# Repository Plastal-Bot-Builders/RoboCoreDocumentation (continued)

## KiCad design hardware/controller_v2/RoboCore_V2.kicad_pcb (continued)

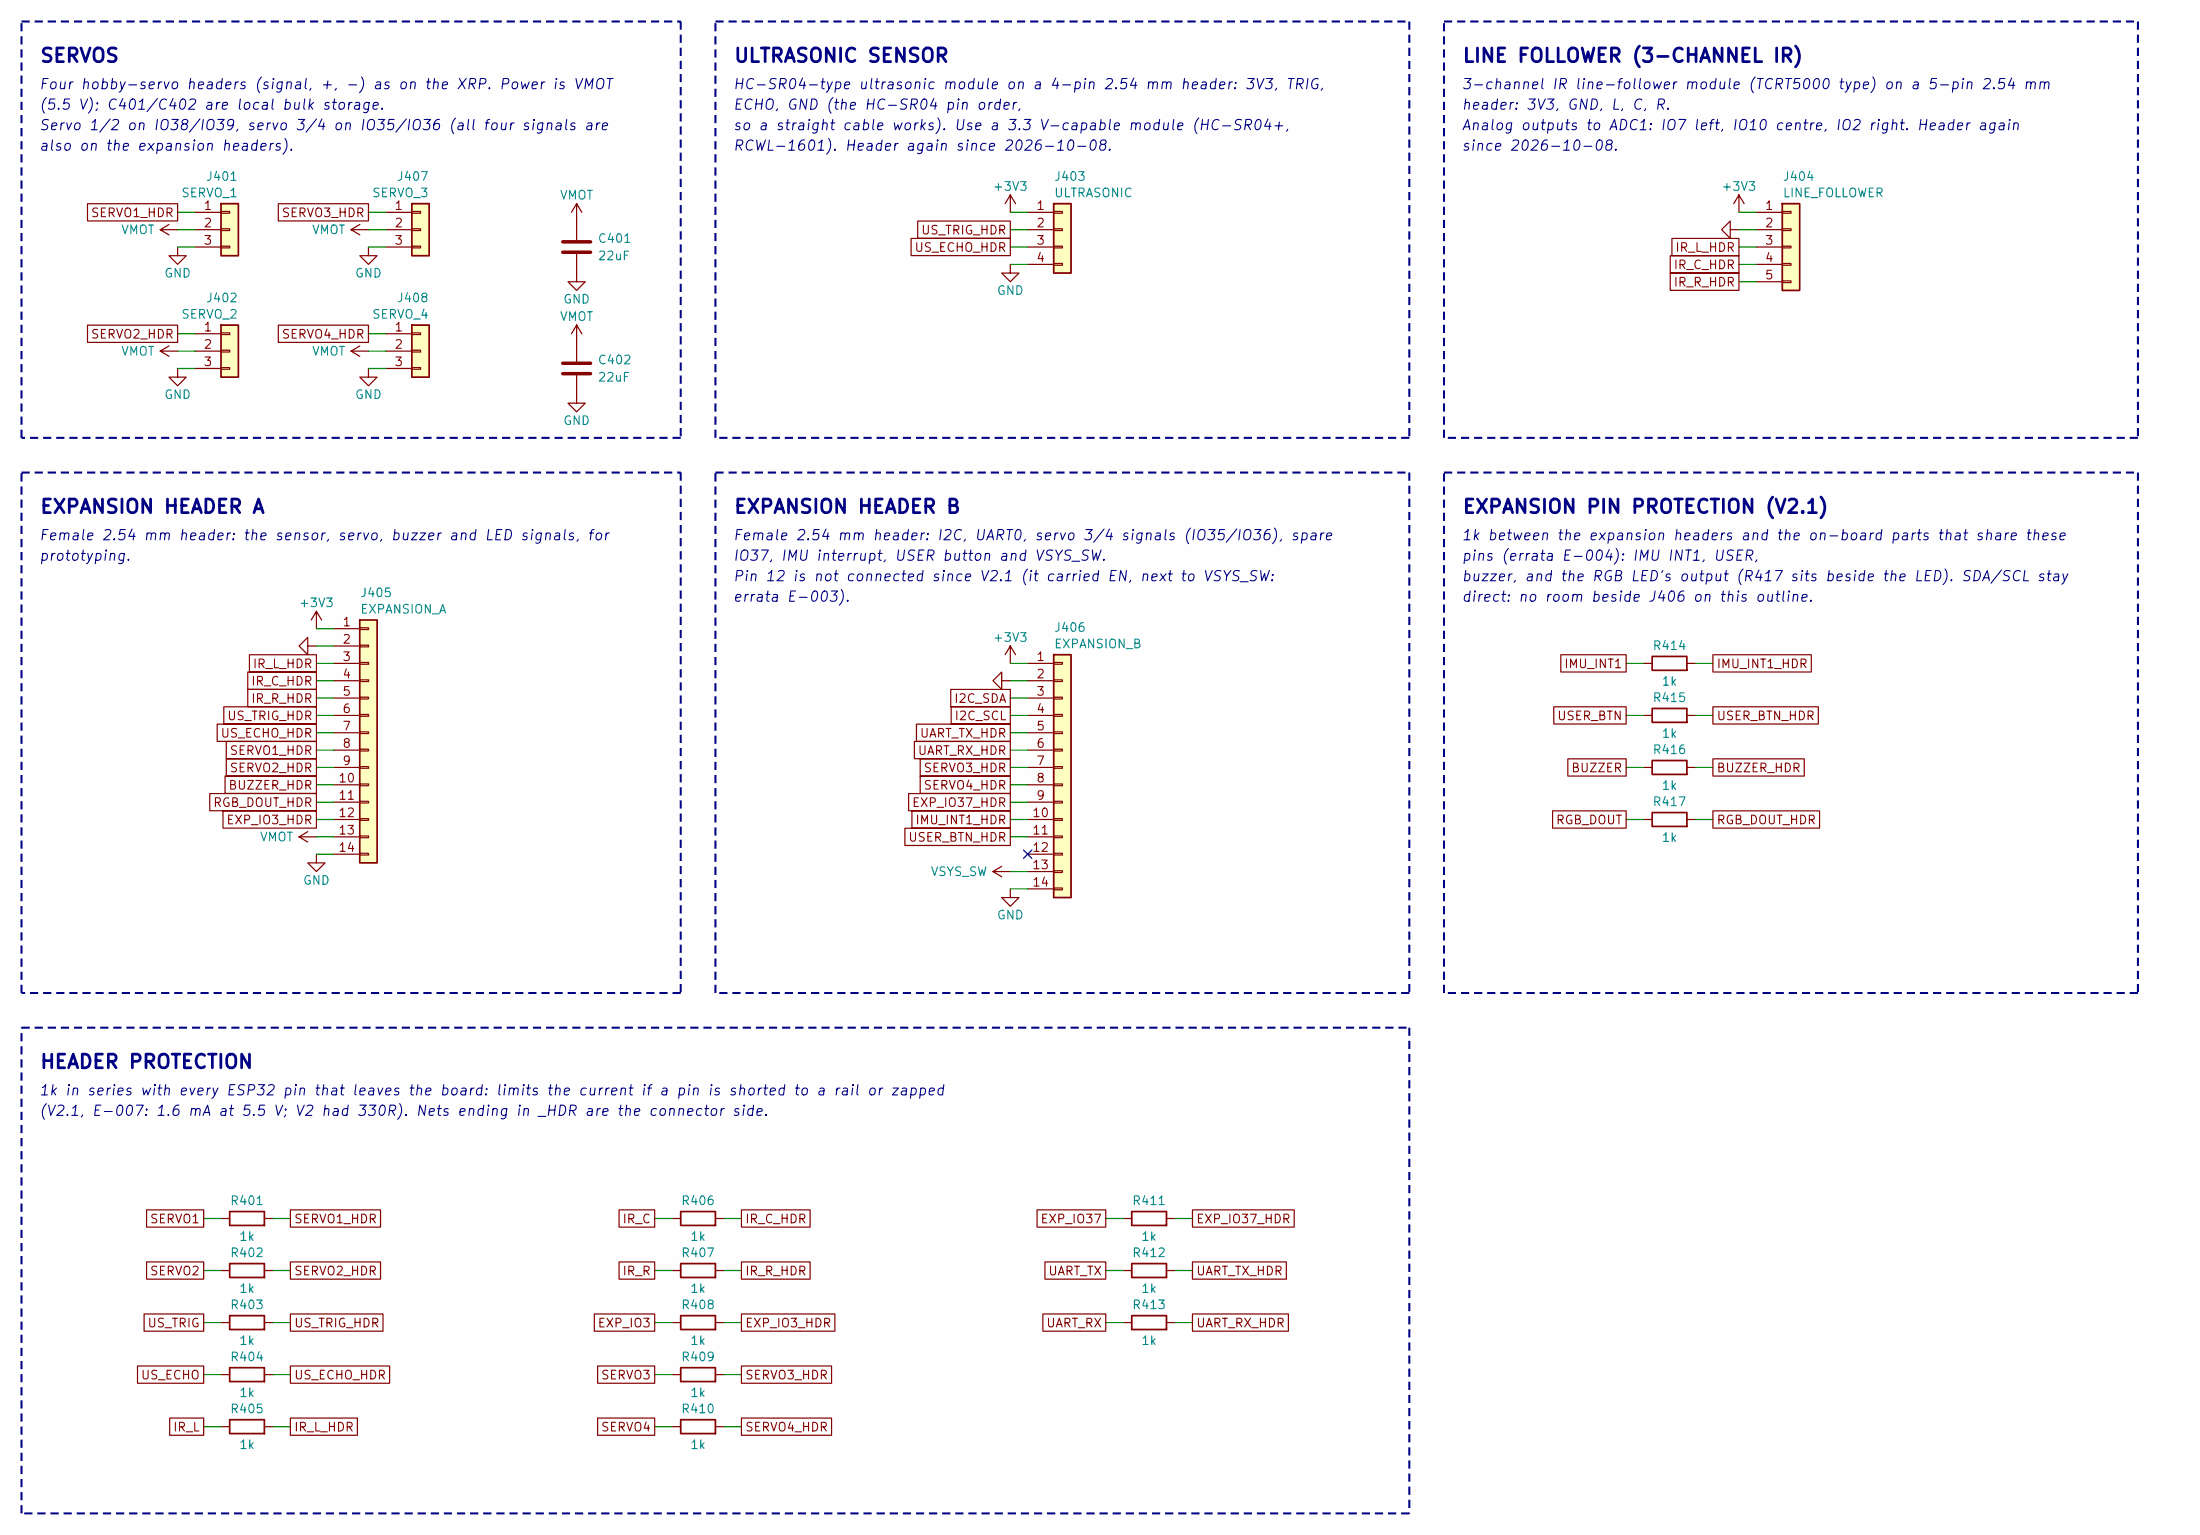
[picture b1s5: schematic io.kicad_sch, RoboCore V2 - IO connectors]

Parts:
C401, C402: 22uF; C_1206_3216Metric; LCSC C12891
J401: SERVO_1; PinHeader_1x03_P2.54mm_Vertical; LCSC C52016391
J402: SERVO_2; PinHeader_1x03_P2.54mm_Vertical; LCSC C52016391
J403: ULTRASONIC; PinHeader_1x04_P2.54mm_Vertical; LCSC C52016392
J404: LINE_FOLLOWER; PinHeader_1x05_P2.54mm_Vertical; LCSC C27985190
J405: EXPANSION_A; PinSocket_1x14_P2.54mm_Vertical; LCSC C22373900
J406: EXPANSION_B; PinSocket_1x14_P2.54mm_Vertical; LCSC C22373900
J407: SERVO_3; PinHeader_1x03_P2.54mm_Vertical; LCSC C52016391
J408: SERVO_4; PinHeader_1x03_P2.54mm_Vertical; LCSC C52016391
R401, R402, R403, R404, R405, R406, R407, R408, R409, R410, R411, R412, R413, R414, R415, R416, R417: 1k; R_0402_1005Metric; LCSC C106235

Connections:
+3V3: J403.1, J404.1, J405.1, J406.1; also elsewhere on the board
BUZZER: R416.1; also elsewhere on the board
BUZZER_HDR: J405.10, R416.2
EXP_IO3: R408.1; also elsewhere on the board
EXP_IO3_HDR: J405.12, R408.2
EXP_IO37: R411.1; also elsewhere on the board
EXP_IO37_HDR: J406.9, R411.2
GND: C401.2, C402.2, J401.3, J402.3, J403.4, J404.2, J405.2, J405.14, J406.2, J406.14, J407.3, J408.3; also elsewhere on the board
I2C_SCL: J406.4; also elsewhere on the board
I2C_SDA: J406.3; also elsewhere on the board
IMU_INT1: R414.1; also elsewhere on the board
IMU_INT1_HDR: J406.10, R414.2
IR_C: R406.1; also elsewhere on the board
IR_C_HDR: J404.4, J405.4, R406.2
IR_L: R405.1; also elsewhere on the board
IR_L_HDR: J404.3, J405.3, R405.2
IR_R: R407.1; also elsewhere on the board
IR_R_HDR: J404.5, J405.5, R407.2
RGB_DOUT: R417.1; also elsewhere on the board
RGB_DOUT_HDR: J405.11, R417.2
SERVO1: R401.1; also elsewhere on the board
SERVO1_HDR: J401.1, J405.8, R401.2
SERVO2: R402.1; also elsewhere on the board
SERVO2_HDR: J402.1, J405.9, R402.2
SERVO3: R409.1; also elsewhere on the board
SERVO3_HDR: J406.7, J407.1, R409.2
SERVO4: R410.1; also elsewhere on the board
SERVO4_HDR: J406.8, J408.1, R410.2
UART_RX: R413.1; also elsewhere on the board
UART_RX_HDR: J406.6, R413.2
UART_TX: R412.1; also elsewhere on the board
UART_TX_HDR: J406.5, R412.2
USER_BTN: R415.1; also elsewhere on the board
USER_BTN_HDR: J406.11, R415.2
US_ECHO: R404.1; also elsewhere on the board
US_ECHO_HDR: J403.3, J405.7, R404.2
US_TRIG: R403.1; also elsewhere on the board
US_TRIG_HDR: J403.2, J405.6, R403.2
VMOT: C401.1, C402.1, J401.2, J402.2, J405.13, J407.2, J408.2; also elsewhere on the board
VSYS_SW: J406.13; also elsewhere on the board

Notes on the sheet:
SERVOS
Four hobby-servo headers (signal, +, -) as on the XRP. Power is VMOT
(5.5 V); C401/C402 are local bulk storage.
Servo 1/2 on IO38/IO39, servo 3/4 on IO35/IO36 (all four signals are
also on the expansion headers).
ULTRASONIC SENSOR
HC-SR04-type ultrasonic module on a 4-pin 2.54 mm header: 3V3, TRIG,
ECHO, GND (the HC-SR04 pin order,
so a straight cable works). Use a 3.3 V-capable module (HC-SR04+,
RCWL-1601). Header again since 2026-10-08.
LINE FOLLOWER (3-CHANNEL IR)
3-channel IR line-follower module (TCRT5000 type) on a 5-pin 2.54 mm
header: 3V3, GND, L, C, R.
Analog outputs to ADC1: IO7 left, IO10 centre, IO2 right. Header again
since 2026-10-08.
EXPANSION HEADER A
Female 2.54 mm header: the sensor, servo, buzzer and LED signals, for
prototyping.
EXPANSION HEADER B
Female 2.54 mm header: I2C, UART0, servo 3/4 signals (IO35/IO36), spare
IO37, IMU interrupt, USER button and VSYS_SW.
Pin 12 is not connected since V2.1 (it carried EN, next to VSYS_SW:
errata E-003).
HEADER PROTECTION
1k in series with every ESP32 pin that leaves the board: limits the current if a pin is shorted to a rail or zapped
(V2.1, E-007: 1.6 mA at 5.5 V; V2 had 330R). Nets ending in _HDR are the connector side.
EXPANSION PIN PROTECTION (V2.1)
1k between the expansion headers and the on-board parts that share these
pins (errata E-004): IMU INT1, USER,
buzzer, and the RGB LED's output (R417 sits beside the LED). SDA/SCL stay
direct: no room beside J406 on this outline.

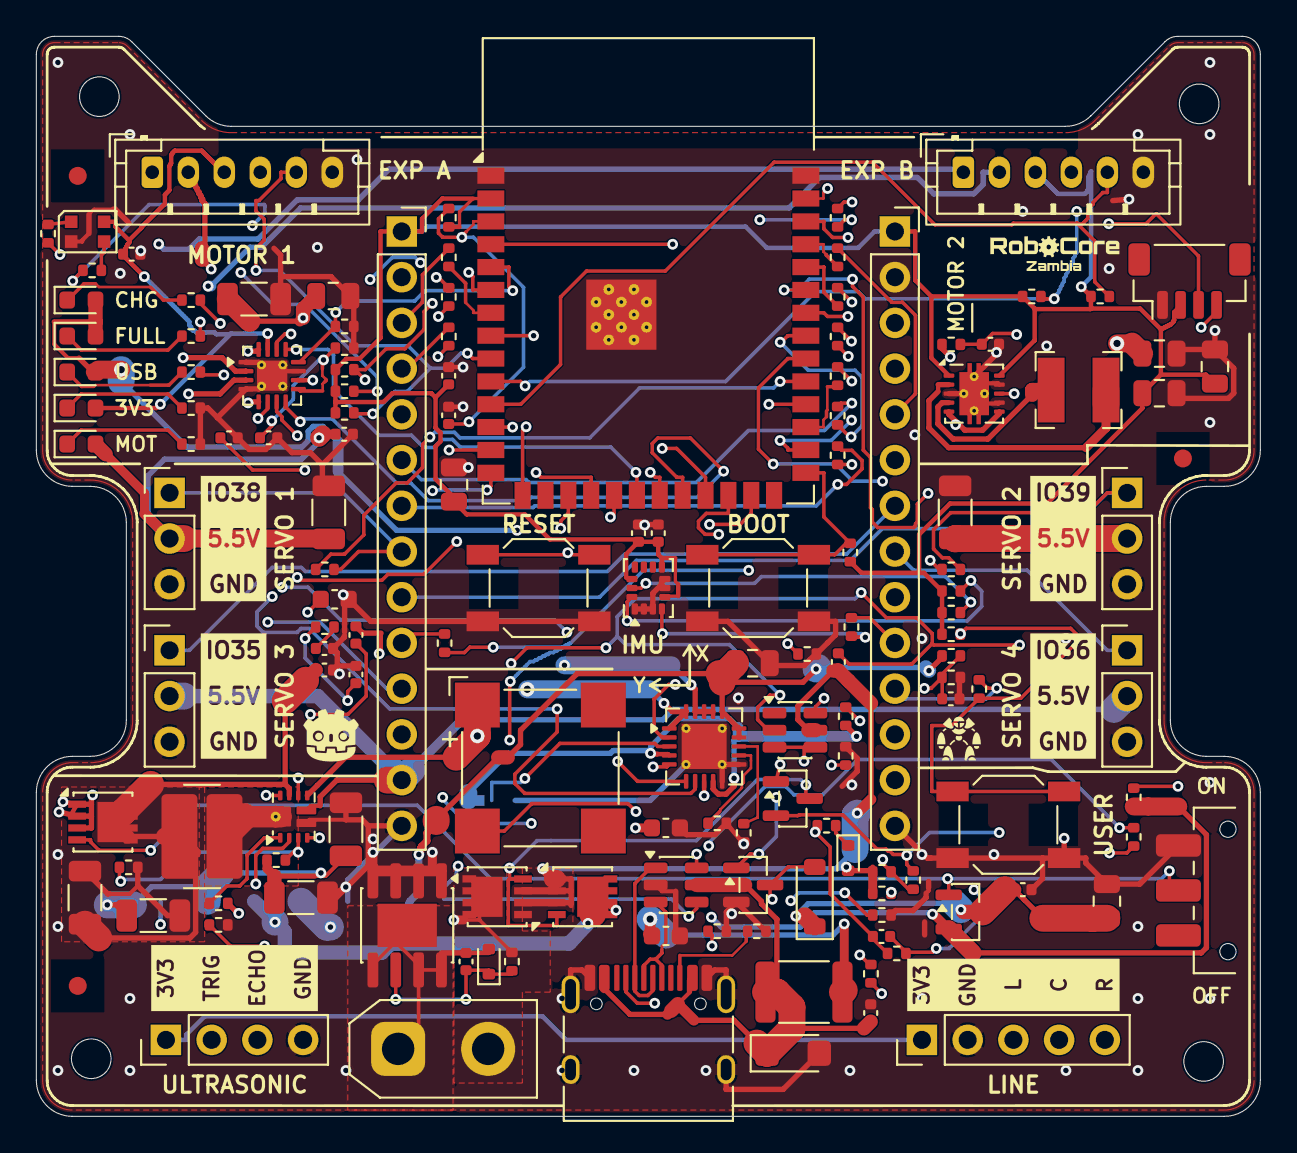
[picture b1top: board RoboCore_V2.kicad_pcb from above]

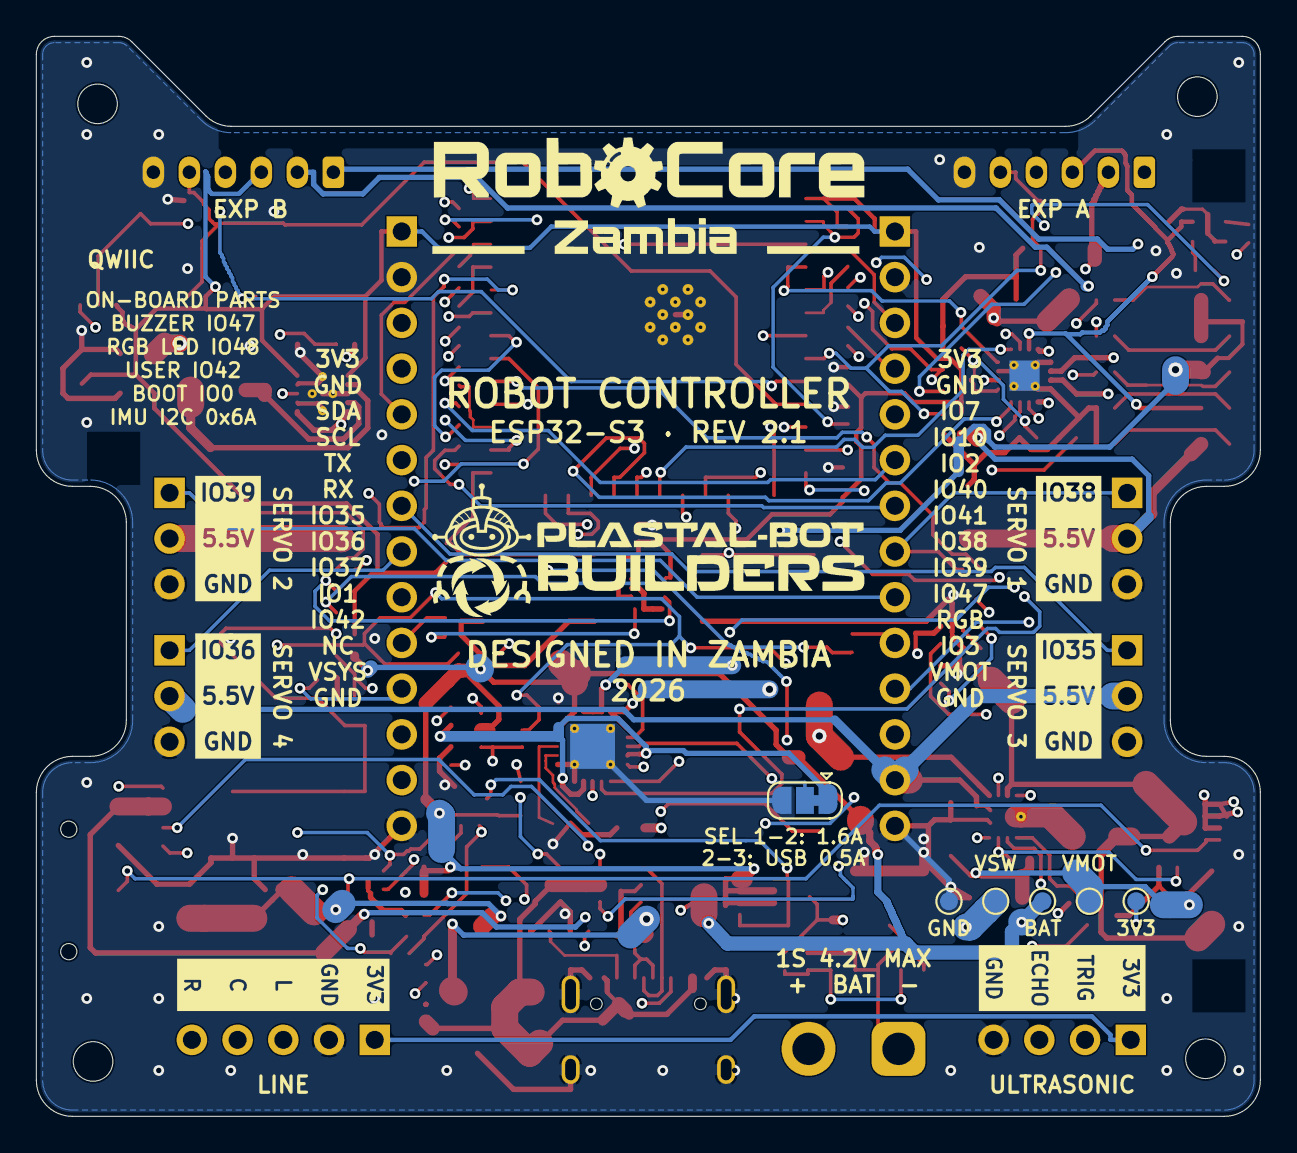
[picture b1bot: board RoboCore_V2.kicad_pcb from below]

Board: 4 copper layers, 68.0 x 60.0 mm, 154 parts (6 on the bottom side), 106 nets.

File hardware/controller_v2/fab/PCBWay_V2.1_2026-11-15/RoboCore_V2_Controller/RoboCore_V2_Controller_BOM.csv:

Item #,Designator,Qty,Manufacturer,Mfg Part #,Description / Value,Package/Footprint,Mounting Type,LCSC Part #,Notes
1,BZ201,1,Same Sky (CUI),CMT-8504-100-SMT-TR,Magnetic buzzer 8.5 mm (CMT-8504-100-SMT),MagneticBuzzer_CUI_CMT-8504-100-SMT,SMD,C22359707,"LCSC had only 12 (2026-10-07); Digi-Key has 30,000+."
2,"C101,C106,C107,C112,C114,C120,C122,C202,C204,C205,C206,C302",12,Samsung,CL05B104KB5NNNC,Ceramic capacitor 100nF 50V X7R ±10% 0402 (0.1uF),C_0402_1005Metric,SMD,C960916,
3,C102,1,Samsung,CL10A105KA8NNNC,Ceramic capacitor 1uF 25V X5R ±10% 0603 (1uF),C_0603_1608Metric,SMD,C5673,
4,C103,1,Samsung,CL10A106MO8NQNC,Ceramic capacitor 10uF 16V X5R ±20% 0603 (10uF),C_0603_1608Metric,SMD,C92487,
5,C104,1,Samsung,CL21A475KAQNNNE,Ceramic capacitor 4.7uF 25V X5R ±10% 0805 (4.7uF),C_0805_2012Metric,SMD,C1779,
6,"C105,C108,C301",3,Samsung,CL21A106KOQNNNE,Ceramic capacitor 10uF 16V X5R ±10% 0805 (10uF),C_0805_2012Metric,SMD,C1713,
7,"C109,C110,C201",3,Samsung,CL21A226MAQNNNE,Ceramic capacitor 22uF 25V X5R ±20% 0805 (22uF),C_0805_2012Metric,SMD,C45783,
8,"C111,C117,C118,C119,C303,C401,C402",7,Samsung,CL31A226KAHNNNE,Ceramic capacitor 22uF 25V X5R ±10% 1206 (22uF),C_1206_3216Metric,SMD,C12891,
9,C113,1,Samsung,CL10A225KO8NNNC,Ceramic capacitor 2.2uF 16V X5R ±10% 0603 (2.2uF),C_0603_1608Metric,SMD,C23630,
10,C115,1,Samsung,CL05B103KB5NNNC,Ceramic capacitor 10nF 50V X7R ±10% 0402 (10nF),C_0402_1005Metric,SMD,C15195,
11,C116,1,Samsung,CL05C220JB5NNNC,Ceramic capacitor 22pF 50V C0G ±5% 0402 (22pF),C_0402_1005Metric,SMD,C70464,
12,"C121,C203",2,Samsung,CL05A105KA5NNNC,Ceramic capacitor 1uF 25V X5R ±10% 0402 (1uF),C_0402_1005Metric,SMD,C16193167,
13,"C304,C305",2,Samsung,CL05B102KB5NNNC,Ceramic capacitor 1nF 50V X7R ±10% 0402 (1nF),C_0402_1005Metric,SMD,C14442,
14,"D101,D105",2,Lite-On,LTST-C191KRKT,LED red 0603 (RED),LED_0603_1608Metric,SMD,C125099,
15,"D102,D104",2,Lite-On,LTST-C191KGKT,LED green 0603 (GREEN),LED_0603_1608Metric,SMD,C125098,
16,D103,1,Lite-On,LTST-C191TBKT,LED blue 0603 (BLUE),LED_0603_1608Metric,SMD,C99290,
17,D106,1,Littelfuse,SMF5.0A,TVS diode 5 V (SMF5.0A),D_SMF,SMD,C151296,
18,D107,1,Vishay,1N4148WS-E3-08,Switching diode (1N4148WS),D_SOD-323,SMD,C129905,
19,D201,1,Worldsemi,WS2812B-2020-V6,Addressable RGB LED 2020 (WS2812B-2020),LED_WS2812B-2020_PLCC4_2.0x2.0mm,SMD,C52917434,
20,D202,1,Diodes Inc,1N4148W-7-F,Switching diode (1N4148W),D_SOD-123,SMD,C83528,
21,F101,1,Bourns,MF-MSMF150/24X-2,PTC resettable fuse 1.5 A (1.5A),Fuse_1812_4532Metric,SMD,C78695,
22,J101,1,HRO,TYPE-C-31-M-12,"USB-C receptacle, 16 pin (TYPE-C-31-M-12)",USB_C_Receptacle_HRO_TYPE-C-31-M-12,SMD,C165948,
23,J102,1,AMASS,XT30UPB-M,"Battery connector XT30, male, vertical (XT30UPB-M)",AMASS_XT30UPB-M_1x02_P5.0mm_Vertical,THT,C428721,"Through-hole, top side."
24,J201,1,JST,BM04B-SRSS-TB,JST SH 4-pin vertical header (Qwiic),JST_SH_BM04B-SRSS-TB_1x04-1MP_P1.00mm_Vertical,SMD,C160390,
25,"J301,J302",2,JST,BM06B-SRSS-TB,JST SH 6-pin vertical header (MOTOR_1 / MOTOR_2),JST_SH_BM06B-SRSS-TB_1x06-1MP_P1.00mm_Vertical_XRP,SMD,C160392,
26,"J401,J402,J407,J408",4,hanxia,HX PH254-01-03-Z-L11.5,"Pin header 1x3, 2.54 mm, straight (SERVO_1 / SERVO_2 / SERVO_3 / SERVO_4)",PinHeader_1x03_P2.54mm_Vertical,THT,C52016391,"Through-hole, top side, short end in the board (6 mm pin up)."
27,J403,1,hanxia,HX PH254-01-04-Z-L11.5,ULTRASONIC (ULTRASONIC),PinHeader_1x04_P2.54mm_Vertical,THT,C52016392,
28,J404,1,Hong Cheng,HC-PZ254-11.5L-1x5PZ,LINE_FOLLOWER (LINE_FOLLOWER),PinHeader_1x05_P2.54mm_Vertical,THT,C27985190,
29,"J405,J406",2,Hong Cheng,HC-PM254-8.5H-1x14PZ,"Female socket 1x14, 2.54 mm, 8.5 mm tall (EXPANSION_A / EXPANSION_B)",PinSocket_1x14_P2.54mm_Vertical,THT,C22373900,"Through-hole, top side."
30,L101,1,Bourns,SRN4018-2R2M,Power inductor 2.2 uH (2.2uH),L_Bourns-SRN4018,SMD,C913207,
31,L102,1,Bourns,SRP5030CA-2R2M,Power inductor 2.2 uH (2.2uH),L_Bourns_SRP5030CA,SMD,C2046809,
32,Q101,1,Alpha & Omega,AO3401A,P-channel MOSFET 30 V (AO3401A),SOT-23,SMD,C15127,
33,"Q102,Q103,Q104",3,Vishay,SI7655DN-T1-GE3,"P-channel MOSFET, PowerPAK 1212-8 (SI7655DN)",Vishay_PowerPAK_1212-8_Single,SMD,C727830,
34,"Q105,Q201",2,Alpha & Omega,AO3400A,N-channel MOSFET 30 V (AO3400A),SOT-23,SMD,C20917,
35,"R101,R102",2,UNI-ROYAL,0402WGF5101TCE,Chip resistor 5.1kΩ ±1% 0402 (5.1k),R_0402_1005Metric,SMD,C25905,
36,"R103,R106,R201,R202,R203,R303,R304,R305,R306,R307",10,UNI-ROYAL,0402WGF1002TCE,Chip resistor 10kΩ ±1% 0402 (10k),R_0402_1005Metric,SMD,C25744,
37,R104,1,UNI-ROYAL,0402WGF2673TCE,Chip resistor 267kΩ ±1% 0402 (267k),R_0402_1005Metric,SMD,C270622,
38,"R105,R107,R108,R109,R119,R401,R402,R403,R404,R405,R406,R407,R408,R409,R410,R411,R412,R413,R414,R415,R416,R417",22,YAGEO,RC0402FR-071KL,Chip resistor 1kΩ ±1% 0402 (1k),R_0402_1005Metric,SMD,C106235,
39,"R110,R117,R118,R121,R122,R123,R206",7,UNI-ROYAL,0402WGF1003TCE,Chip resistor 100kΩ ±1% 0402 (100k),R_0402_1005Metric,SMD,C25741,
40,"R111,R205",2,YAGEO,RC0402FR-07100RL,Chip resistor 100Ω ±1% 0402 (100),R_0402_1005Metric,SMD,C106232,
41,R112,1,UNI-ROYAL,0402WGF9101TCE,Chip resistor 9.1kΩ ±1% 0402 (9.1k),R_0402_1005Metric,SMD,C25926,
42,"R113,R115",2,UNI-ROYAL,0402WGF3003TCE,Chip resistor 300kΩ ±1% 0402 (300k),R_0402_1005Metric,SMD,C25774,
43,R114,1,UNI-ROYAL,0402WGF8452TCE,Chip resistor 84.5kΩ ±1% 0402 (84.5k),R_0402_1005Metric,SMD,C26988,
44,R116,1,UNI-ROYAL,0402WGF2003TCE,Chip resistor 200kΩ ±1% 0402 (200k),R_0402_1005Metric,SMD,C25764,
45,R120,1,UNI-ROYAL,0402WGF2201TCE,Chip resistor 2.2kΩ ±1% 0402 (2.2k),R_0402_1005Metric,SMD,C25879,
46,R124,1,UNI-ROYAL,0402WGF3303TCE,Chip resistor 330kΩ ±1% 0402 (330k),R_0402_1005Metric,SMD,C25778,
47,R125,1,UNI-ROYAL,0402WGF1004TCE,Chip resistor 1MΩ ±1% 0402 (1M),R_0402_1005Metric,SMD,C26083,
48,R126,1,UNI-ROYAL,0402WGF9532TCE,Chip resistor 95.3kΩ ±1% 0402 (95.3k),R_0402_1005Metric,SMD,C26990,
49,R204,1,YAGEO,RC0402FR-0733RL,Chip resistor 33Ω ±1% 0402 (33),R_0402_1005Metric,SMD,C138002,
50,"R207,R208",2,UNI-ROYAL,0402WGF4701TCE,Chip resistor 4.7kΩ ±1% 0402 (4.7k),R_0402_1005Metric,SMD,C25900,
51,"R301,R302",2,UNI-ROYAL,0402WGF1652TCE,Chip resistor 16.5kΩ ±1% 0402 (16.5k),R_0402_1005Metric,SMD,C25857,
52,SW101,1,C&K,JS102011SAQN,"Slide switch SPDT, side-actuated (ON/OFF)",SW_SPDT_CK_JS102011SAQN,SMD,C221660,"LCSC shows 0 stock (2026-10-07); Digi-Key has 54,000+. Lever must overhang the board edge as drawn."
53,"SW201,SW202,SW203",3,Alps Alpine,SKQGADE010,Tactile switch 5.2 x 5.2 mm (RESET / BOOT / USER),SW_SPST_SKQG_WithoutStem,SMD,C116647,
54,U101,1,STMicroelectronics,USBLC6-2SC6,"USB ESD protection, 2 lines (USBLC6-2SC6)",SOT-23-6,SMD,C7519,
55,U102,1,Microchip,MCP73871-2CCI/ML,"Li-ion charger with power path, 4.20 V charge voltage (MCP73871-2CCI/ML)",QFN-20-1EP_4x4mm_P0.5mm_EP2.5x2.5mm_ThermalVias,SMD,C5121473,Must be the -2 version (4.20 V). Other suffixes charge to the wrong voltage.
56,U103,1,Texas Instruments,TPS63001DRCR,"Buck-boost converter, 3.3 V fixed (TPS63001DRCR)",Texas_DRC0010J_ThermalVias,SMD,C28060,
57,U104,1,Texas Instruments,TPS61089RNRR,"Boost converter, 7 A switch (TPS61089RNRR)",Texas_VQFN-RNR0011A-11,SMD,C165129,
58,U105,1,Texas Instruments,TPS3700DDCR,Window voltage supervisor (TPS3700),TSOT-23-6,SMD,C33002,
59,U201,1,Espressif,ESP32-S3-WROOM-1-N8R2,"Wi-Fi/BLE module, 8 MB flash, 2 MB quad PSRAM (ESP32-S3-WROOM-1-N8R2)",ESP32-S3-WROOM-1,SMD,C2913204,Alternative: -N16R2. Do NOT use R8 / R16V (octal PSRAM) versions.
60,U202,1,STMicroelectronics,LSM6DSOXTR,"6-axis IMU (accelerometer + gyroscope), I2C (LSM6DSOX)",LGA-14_3x2.5mm_P0.5mm_LayoutBorder3x4y,SMD,C481766,
61,U301,1,Texas Instruments,DRV8411ARTER,"Dual H-bridge motor driver, 4 A (DRV8411ARTER)",WQFN-16-1EP_3x3mm_P0.5mm_EP1.68x1.68mm_ThermalVias,SMD,C18816315,

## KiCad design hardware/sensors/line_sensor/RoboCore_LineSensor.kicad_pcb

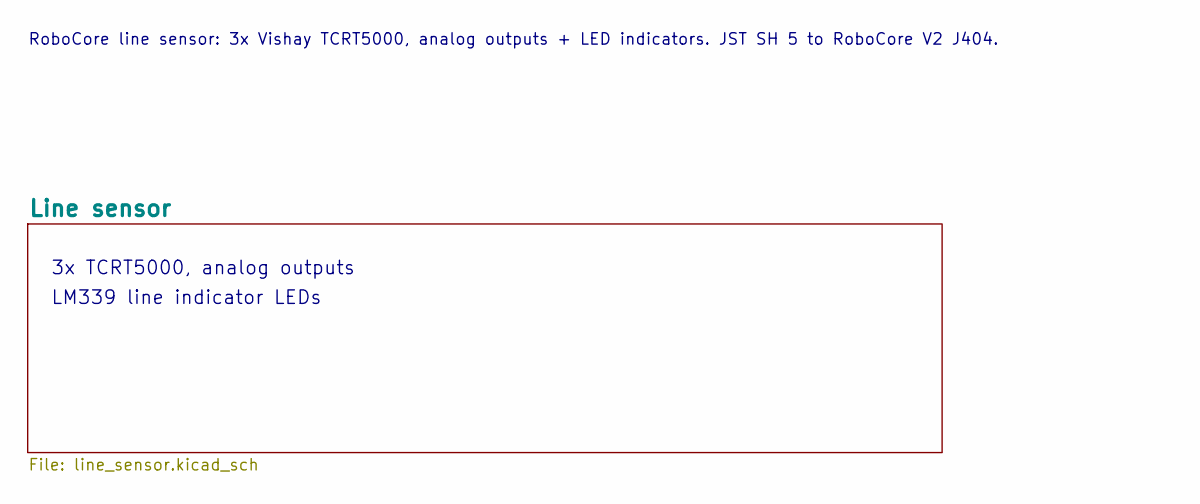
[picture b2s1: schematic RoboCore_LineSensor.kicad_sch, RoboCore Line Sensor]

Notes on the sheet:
3x TCRT5000, analog outputs
LM339 line indicator LEDs
RoboCore line sensor: 3x Vishay TCRT5000, analog outputs + LED indicators. JST SH 5 to RoboCore V2 J404.

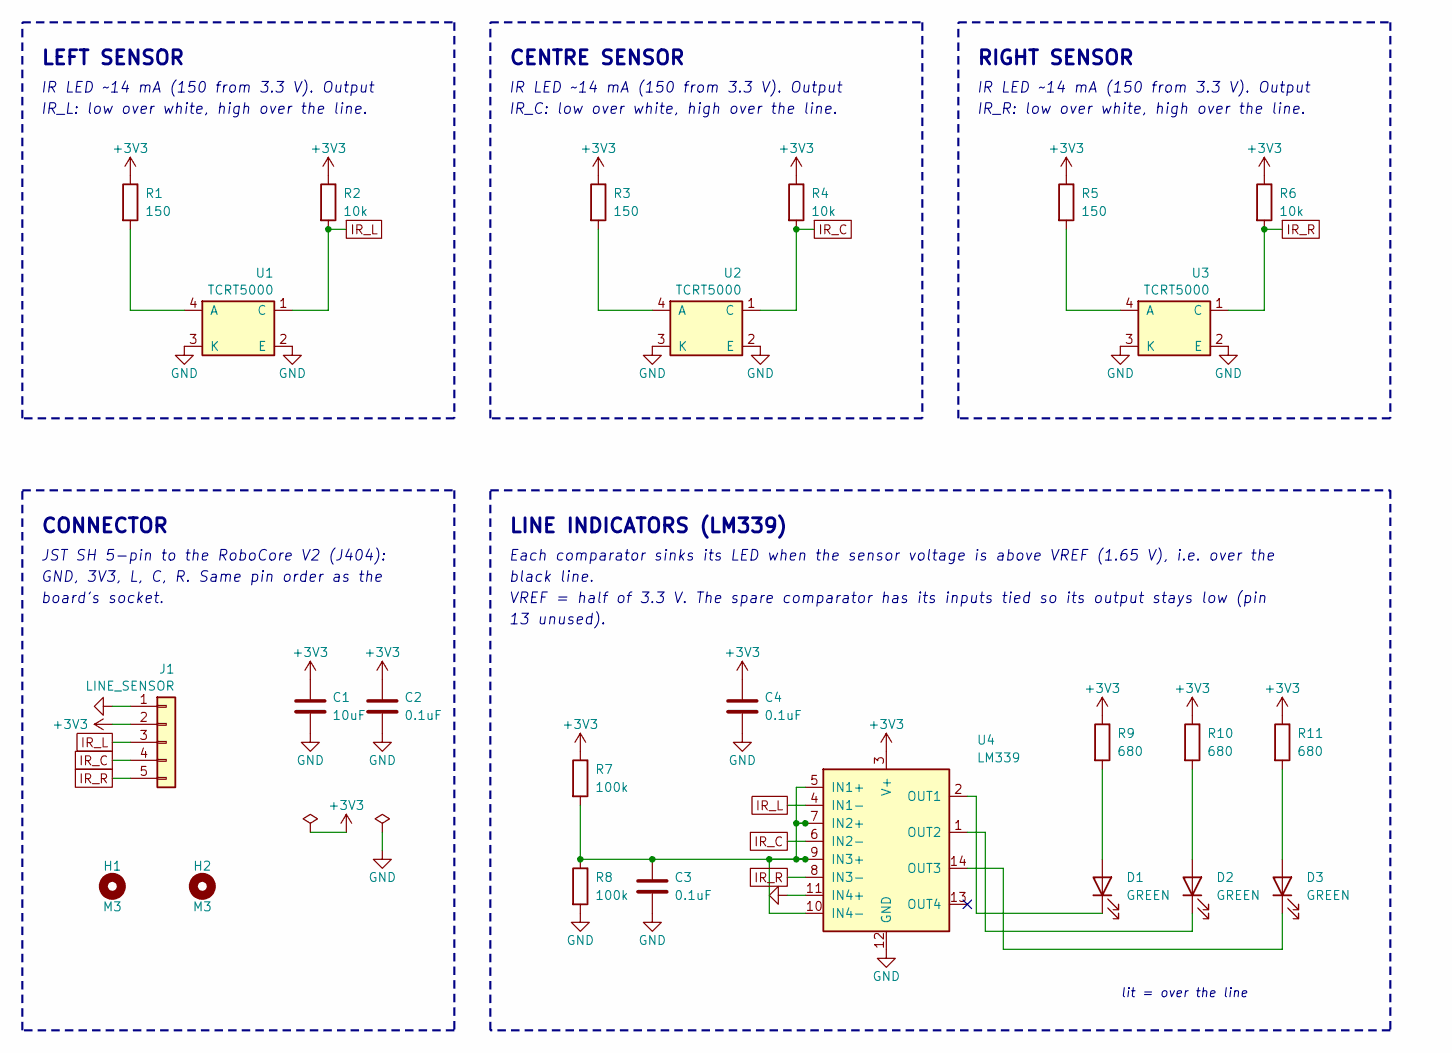
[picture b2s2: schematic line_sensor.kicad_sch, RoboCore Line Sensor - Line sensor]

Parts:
C1: 10uF; C_0805_2012Metric; LCSC C1713
C2, C3, C4: 0.1uF; C_0603_1608Metric; LCSC C1591
D1, D2, D3: GREEN; LED_0603_1608Metric; LCSC C125098
H1, H2: M3; MountingHole_3.2mm_M3
J1: LINE_SENSOR; JST_SH_BM05B-SRSS-TB_1x05-1MP_P1.00mm_Vertical; LCSC C160391
R1, R3, R5: 150; R_0603_1608Metric; LCSC C22808
R2, R4, R6: 10k; R_0603_1608Metric; LCSC C98220
R7, R8: 100k; R_0603_1608Metric; LCSC C25803
R9, R10, R11: 680; R_0603_1608Metric; LCSC C23228
U1, U2, U3: TCRT5000; Vishay_TCRT5000; LCSC C2984661
U4: LM339; SOIC-14_3.9x8.7mm_P1.27mm; LCSC C2829428

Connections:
+3V3: C1.1, C2.1, C4.1, J1.2, R1.1, R2.1, R3.1, R4.1, R5.1, R6.1, R7.1, R9.1, R10.1, R11.1, U4.3 (V+)
GND: C1.2, C2.2, C3.2, C4.2, J1.1, R8.2, U1.2 (E), U1.3 (K), U2.2 (E), U2.3 (K), U3.2 (E), U3.3 (K), U4.11 (IN4+), U4.12 (GND)
IR_C: J1.4, R4.2, U2.1 (C), U4.6 (IN2-)
IR_L: J1.3, R2.2, U1.1 (C), U4.4 (IN1-)
IR_R: J1.5, R6.2, U3.1 (C), U4.8 (IN3-)
unnamed: D1.2 (A), R9.2
unnamed: D1.1 (K), U4.2 (OUT1)
unnamed: D2.2 (A), R10.2
unnamed: D2.1 (K), U4.1 (OUT2)
unnamed: D3.2 (A), R11.2
unnamed: D3.1 (K), U4.14 (OUT3)
unnamed: R1.2, U1.4 (A)
unnamed: R3.2, U2.4 (A)
unnamed: R5.2, U3.4 (A)
unnamed: C3.1, R7.2, R8.1, U4.5 (IN1+), U4.7 (IN2+), U4.9 (IN3+), U4.10 (IN4-)

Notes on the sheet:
LEFT SENSOR
IR LED ~14 mA (150 from 3.3 V). Output
IR_L: low over white, high over the line.
CENTRE SENSOR
IR_C: low over white, high over the line.
RIGHT SENSOR
IR_R: low over white, high over the line.
CONNECTOR
JST SH 5-pin to the RoboCore V2 (J404):
GND, 3V3, L, C, R. Same pin order as the
board's socket.
LINE INDICATORS (LM339)
Each comparator sinks its LED when the sensor voltage is above VREF (1.65 V), i.e. over the
black line.
VREF = half of 3.3 V. The spare comparator has its inputs tied so its output stays low (pin
13 unused).
lit = over the line

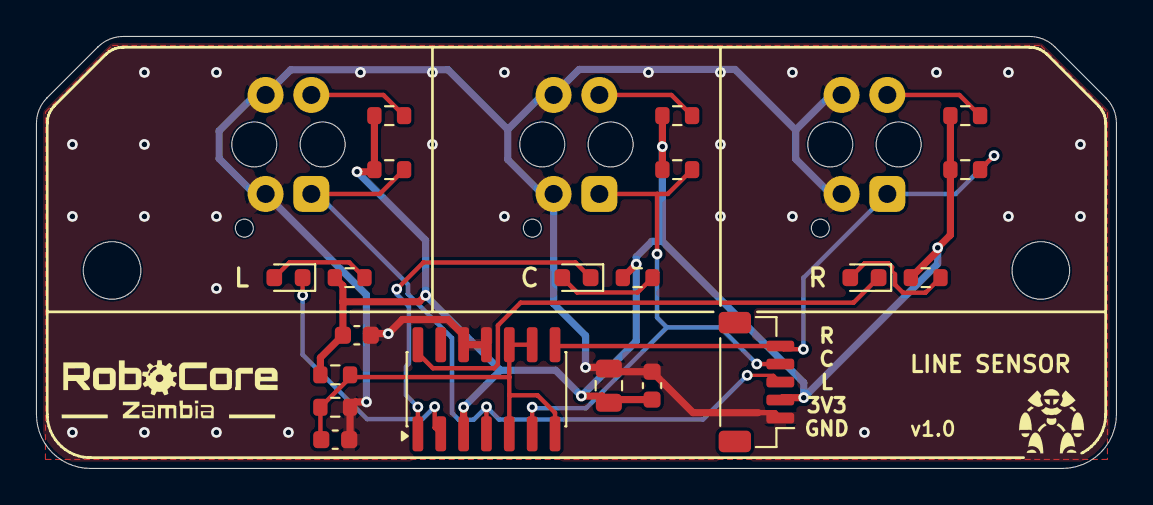
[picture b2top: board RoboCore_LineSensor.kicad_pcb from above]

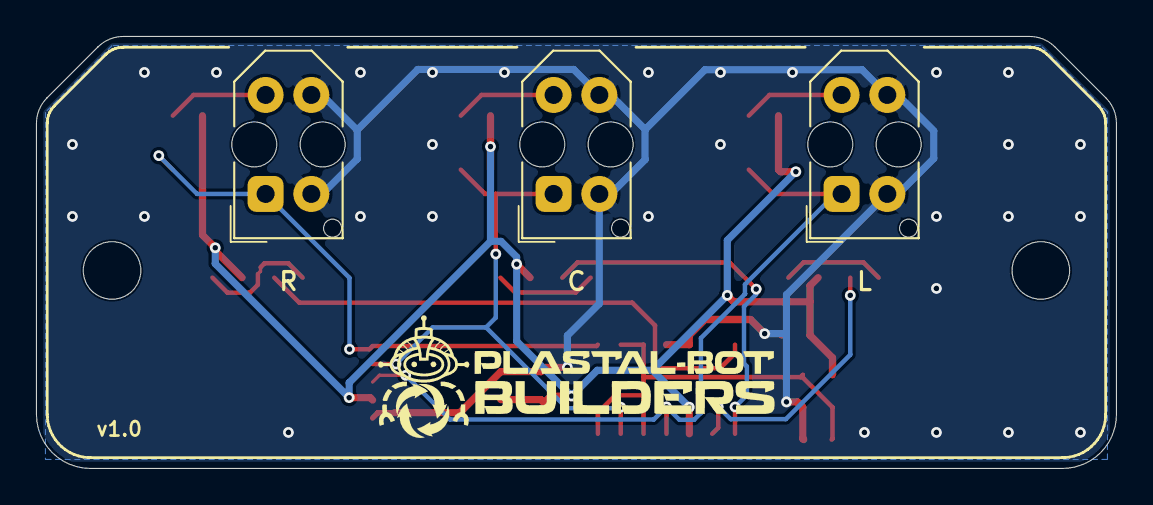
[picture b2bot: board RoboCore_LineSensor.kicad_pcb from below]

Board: 2 copper layers, 60.0 x 24.0 mm, 25 parts (3 on the bottom side), 15 nets.

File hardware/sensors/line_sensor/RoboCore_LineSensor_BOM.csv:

"Refs","Value","Footprint","Manufacturer","MPN","LCSC","Alternative","Qty"
"C1","10uF","Capacitor_SMD:C_0805_2012Metric","","","","","1"
"C2-C4","0.1uF","Capacitor_SMD:C_0603_1608Metric","","","","","3"
"D1-D3","GREEN","LED_SMD:LED_0603_1608Metric","Lite-On","LTST-C191KGKT","C125098","","3"
"J1","LINE_SENSOR","Connector_JST:JST_SH_BM05B-SRSS-TB_1x05-1MP_P1.00mm_Vertical","JST","BM05B-SRSS-TB","C160391","","1"
"R1,R3,R5","150","Resistor_SMD:R_0603_1608Metric","","","","","3"
"R2,R4,R6","10k","Resistor_SMD:R_0603_1608Metric","","","","","3"
"R7,R8","100k","Resistor_SMD:R_0603_1608Metric","","","","","2"
"R9-R11","680","Resistor_SMD:R_0603_1608Metric","","","","","3"
"U1-U3","TCRT5000","OptoDevice:Vishay_TCRT5000","Vishay","TCRT5000","C2984661","TCRT5000L (long leads)","3"
"U4","LM339","Package_SO:SOIC-14_3.9x8.7mm_P1.27mm","JSCJ","LM339","C2829428","TI LM339DR","1"

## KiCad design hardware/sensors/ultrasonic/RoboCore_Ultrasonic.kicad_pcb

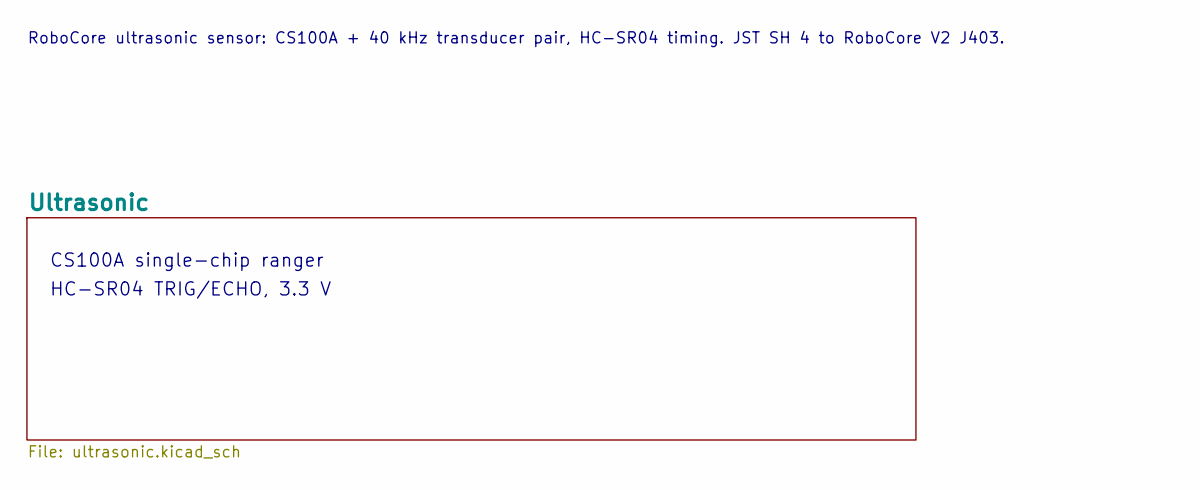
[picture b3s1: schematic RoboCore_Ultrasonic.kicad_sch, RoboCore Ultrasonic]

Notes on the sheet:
CS100A single-chip ranger
HC-SR04 TRIG/ECHO, 3.3 V
RoboCore ultrasonic sensor: CS100A + 40 kHz transducer pair, HC-SR04 timing. JST SH 4 to RoboCore V2 J403.

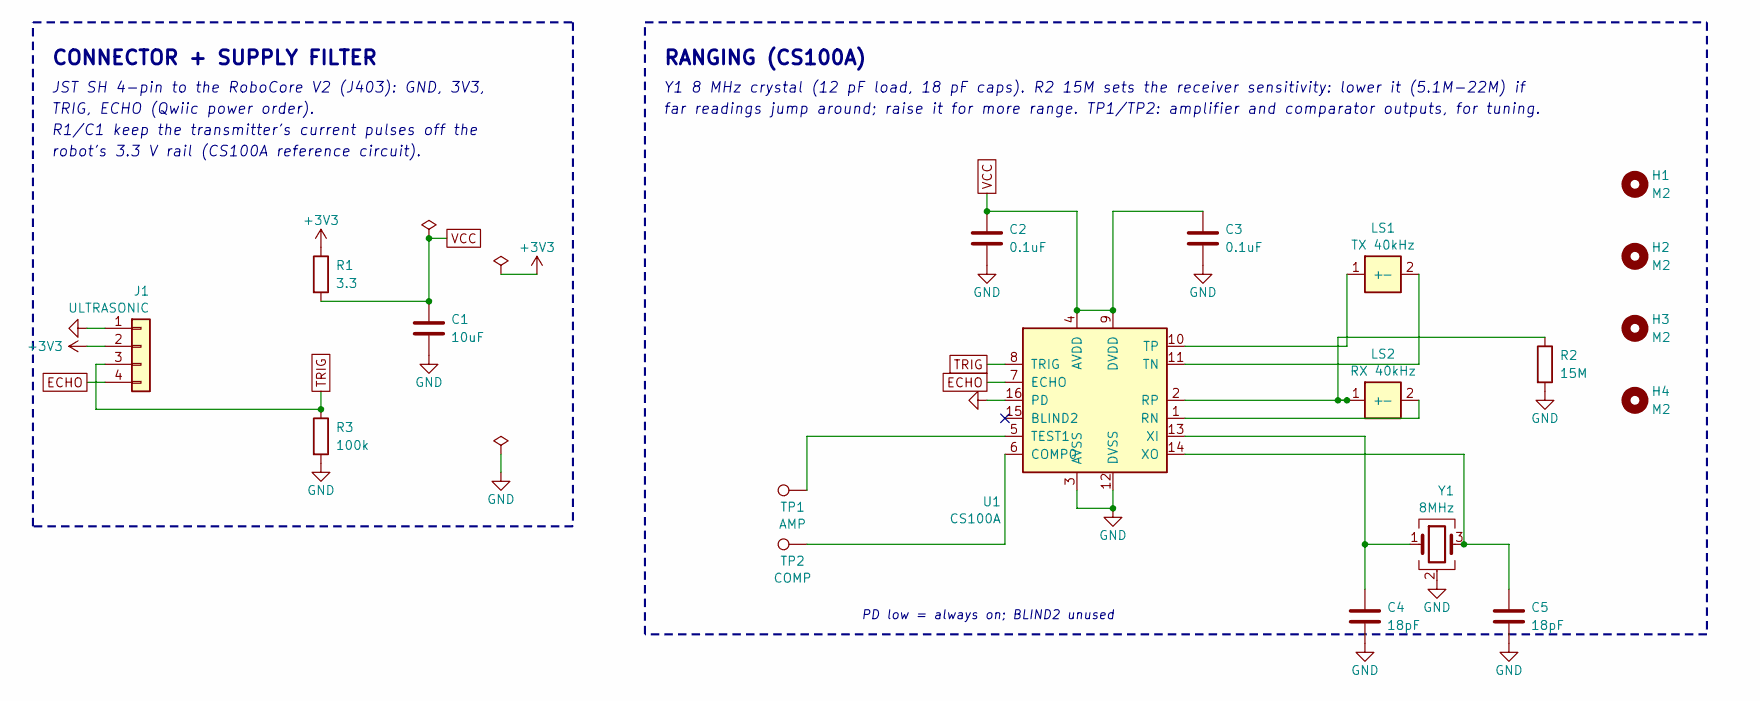
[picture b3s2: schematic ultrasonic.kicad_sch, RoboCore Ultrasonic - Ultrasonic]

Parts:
C1: 10uF; C_0805_2012Metric; LCSC C1713
C2, C3: 0.1uF; C_0603_1608Metric; LCSC C1591
C4, C5: 18pF; C_0603_1608Metric; LCSC C1647
H1, H2, H3, H4: M2; MountingHole_2.2mm_M2
J1: ULTRASONIC; JST_SH_BM04B-SRSS-TB_1x04-1MP_P1.00mm_Vertical; LCSC C160390
LS1: TX 40kHz; Ultrasonic_Transducer_D16.0mm_P10.00mm; LCSC C17701106
LS2: RX 40kHz; Ultrasonic_Transducer_D16.0mm_P10.00mm; LCSC C17701107
R1: 3.3; R_0603_1608Metric; LCSC C137725
R2: 15M; R_0603_1608Metric; LCSC C80615
R3: 100k; R_0603_1608Metric; LCSC C25803
TP1: AMP; TestPoint_Pad_D1.0mm
TP2: COMP; TestPoint_Pad_D1.0mm
U1: CS100A; SOIC-16_3.9x9.9mm_P1.27mm
Y1: 8MHz; Crystal_SMD_3225-4Pin_3.2x2.5mm; LCSC C2842191

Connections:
+3V3: J1.2, R1.1
ECHO: J1.4, U1.7 (ECHO)
GND: C1.2, C2.2, C3.2, C4.2, C5.2, J1.1, R2.2, R3.2, U1.3 (AVSS), U1.12 (DVSS), U1.16 (PD), Y1.2 (G), Y1.4 (G)
unnamed: LS1.1 (+), U1.10 (TP)
unnamed: LS1.2 (-), U1.11 (TN)
unnamed: LS2.1 (+), R2.1, U1.2 (RP)
unnamed: LS2.2 (-), U1.1 (RN)
unnamed: TP2.1, U1.6 (COMP0)
unnamed: TP1.1, U1.5 (TEST1)
unnamed: C4.1, U1.13 (XI), Y1.1
unnamed: C5.1, U1.14 (XO), Y1.3
TRIG: J1.3, R3.1, U1.8 (TRIG)
VCC: C1.1, C2.1, C3.1, R1.2, U1.4 (AVDD), U1.9 (DVDD)

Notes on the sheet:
CONNECTOR + SUPPLY FILTER
JST SH 4-pin to the RoboCore V2 (J403): GND, 3V3,
TRIG, ECHO (Qwiic power order).
R1/C1 keep the transmitter's current pulses off the
robot's 3.3 V rail (CS100A reference circuit).
RANGING (CS100A)
Y1 8 MHz crystal (12 pF load, 18 pF caps). R2 15M sets the receiver sensitivity: lower it (5.1M-22M) if
far readings jump around; raise it for more range. TP1/TP2: amplifier and comparator outputs, for tuning.
PD low = always on; BLIND2 unused

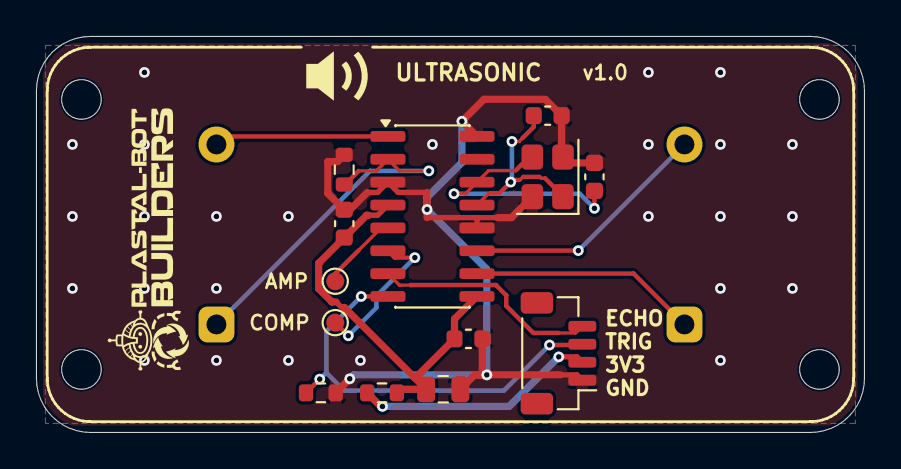
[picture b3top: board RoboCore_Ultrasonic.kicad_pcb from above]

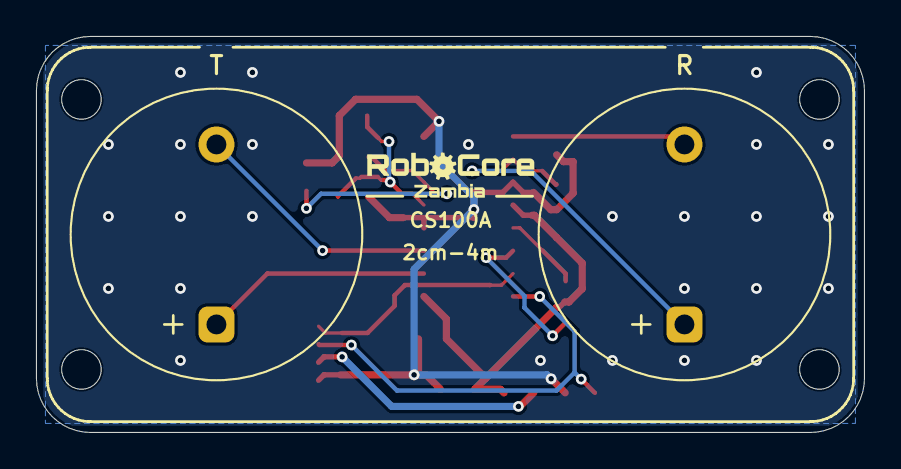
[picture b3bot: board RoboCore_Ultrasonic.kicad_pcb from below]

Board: 2 copper layers, 46.0 x 22.0 mm, 19 parts (2 on the bottom side), 13 nets.

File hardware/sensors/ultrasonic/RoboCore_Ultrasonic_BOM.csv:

"Refs","Value","Footprint","Manufacturer","MPN","LCSC","Alternative","Qty"
"C1","10uF","Capacitor_SMD:C_0805_2012Metric","","","","","1"
"C2,C3","0.1uF","Capacitor_SMD:C_0603_1608Metric","","","","","2"
"C4,C5","18pF","Capacitor_SMD:C_0603_1608Metric","","","","","2"
"J1","ULTRASONIC","Connector_JST:JST_SH_BM04B-SRSS-TB_1x04-1MP_P1.00mm_Vertical","JST","BM04B-SRSS-TB","C160390","","1"
"LS1","TX 40kHz","RoboCoreV2:Ultrasonic_Transducer_D16.0mm_P10.00mm","HYDZ","HY40A16T12-1","C17701106","","1"
"LS2","RX 40kHz","RoboCoreV2:Ultrasonic_Transducer_D16.0mm_P10.00mm","HYDZ","HY40A16R12-1","C17701107","","1"
"R1","3.3","Resistor_SMD:R_0603_1608Metric","","","","","1"
"R2","15M","Resistor_SMD:R_0603_1608Metric","","","","","1"
"R3","100k","Resistor_SMD:R_0603_1608Metric","","","","","1"
"U1","CS100A","Package_SO:SOIC-16_3.9x9.9mm_P1.27mm","Suzhou ShunGuiZhiLian (100sensor.com)","CS100A","","not at LCSC: buy from AliExpress/Alibaba and consign to the assembler","1"
"Y1","8MHz","Crystal:Crystal_SMD_3225-4Pin_3.2x2.5mm","HCI","XC32M4-8.000-F12LJDT","C2842191","","1"
